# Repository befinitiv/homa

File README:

The goal of this project is to create small, cheap and power efficient devices for home automation (HA).

First, a remote controllable wall socket will be built. This will give the basis for deriving other devices for sensing and actuating.

All devices will be communicating via a power efficient 2.4GHz wireless link. For saving cost and power, a proprietary protocol will be used (http://www.nordicsemi.com/eng/Products/2.4GHz-RF/nRF24L01 ).

Power efficiency is a key goal of the project. By using modern approaches for the power supply, the power consumption of these devices will be two orders of magnitude lower than the usual standby power of consumer devices. The user does not have to think about whether or not to add another HA device. In almost every case adding more HA devices will save power.

----
All prices include VAT.
Edit
Battery powered devel board (rev A)

Components: 5.09€
PCB: 55mmx18mm = 0.1dm^2 = 7€ plus 1€ mill cost
Sum: 13.09€
---
Reduced price for 50x pieces:
Components 1.46€ (future electronics)
PCB: 1.60€ (Fischer PCB, reduced width)
Sum: 3.06€
Edit
STM ucboard (rev A)

Components: 8€
PCB: 34mmx14mm = 0.047dm^2 = 3.29€ plus 1€ mill cost
Sum: 12.29€
---
Reduced price for 50x pieces without LEDs, RTC and 64kB uC:
Components: 1.40€ (future electronics)
PCB: 1.19€ (Fischer PCB)
Sum: 2.59€
Edit
Relais board (rev A)

Components: 8.43€
PCB: 34mmx23mm = 0.078dm^2 = 5.46€ plus 1€ mill cost
Sum: 14.89€

Price for 1dm^2 PCB: 70€ (pcb-pool)
Edit
Log

15-03-19 Cedric paid everything to Bennet

----

SettingUpBuildEnv

    Download compiler:
    sudo add-apt-repository ppa:terry.guo/gcc-arm-embedded
    sudo apt-get update
    sudo apt-get install gcc-arm-none-eabi

    Download and install segger software:
    http://www.segger.com/jlink-software.html?step=2&file=JLinkLinuxDEB64_4.82

    Install Eclipse
        Inside of eclipse: Install GDB Hardware Debugging extension http://stm32discovery.nano-age.co.uk/open-source-development-with-the-stm32-discovery/getting-hardware-debuging-working-with-eclipse-and-code-sourcey
        Create a “GDB hardware debugging” configuration and enter the following lines to “Startup→Initialization Commands”:
        monitor flash device STM32F051C8
        monitor speed 1000

-----

h1. Tea1721

See http://www.nxp.com/documents/user_manual/UM10522.pdf

L1: "Reichelt":http://www.reichelt.de/Power-Induktivitaeten-SMD/L-PISG-1-0M/3/index.html?&ACTION=3&LA=2&ARTICLE=86537&GROUPID=3709&artnr=L-PISG+1%2C0M
L2: "Reichelt":http://www.reichelt.de/Power-Induktivitaeten-SMD/L-PISR-1-0M/3/index.html?&ACTION=3&LA=2&ARTICLE=73077&GROUPID=3709&artnr=L-PISR+1%2C0M

D7: "Digikey":http://www.digikey.de/product-detail/de/BZX384-B12,115/568-3810-1-ND/1163091
D4, D6: "Reichelt":http://www.reichelt.de/BY-BYX-EM-ER-Dioden/ES-1JL-SMD/3/index.html?&ACTION=3&LA=446&ARTICLE=95404&GROUPID=2989&artnr=ES+1JL+SMD
D5: "Digikey":http://www.digikey.de/product-detail/de/BYG20J-E3%2FTR/BYG20J-E3%2FTRGICT-ND/2356593
D1: "Reichelt":http://www.reichelt.de/SB-SKE-4F-Dioden/S-1ML-SMD/3/index.html?&ACTION=3&LA=446&ARTICLE=95358&GROUPID=2991&artnr=S+1ML+SMD

C1,C2: "Digikey":http://www.digikey.de/product-detail/de/400PX4R7MEFCTA8X11.5/1189-1633-1-ND/3134590
C3: "Digikey":http://www.digikey.de/product-detail/de/C0603C100K3GACTU/399-8979-1-ND/3522496
C7: "Digikey":http://www.digikey.de/product-detail/de/CL05B103KB5NNNC/1276-1028-1-ND/3889114
C45, C14: "Digikey":http://www.digikey.de/product-detail/de/CL31A225KB9LNNC/1276-2723-1-ND/3890809
C6: "Digikey":http://www.digikey.de/product-detail/de/UVR1C471MPD/493-1043-ND/588784

IC1: "Digikey":http://www.digikey.de/product-detail/de/TEA1721AT%2FN1,118/568-9556-1-ND/3250102

R1: "Digikey":http://www.digikey.de/product-detail/de/CF14JT47R0/CF14JT47R0CT-ND/1830319
R2: "Digikey":http://www.digikey.de/product-detail/de/RC1005F472CS/1276-3466-1-ND/3903569
R3: "Digikey":http://www.digikey.de/product-detail/de/MCR01MRTF1802/RHM18KCDCT-ND/4083706
R4: "Digikey":http://www.digikey.de/product-detail/de/RC1206JR-071RL/311-1.0ERCT-ND/732132
R5: "Digikey":http://www.digikey.de/product-detail/de/RC0603JR-0768KL/311-68KGRCT-ND/729769

SS-Relais: "Digikey":http://www.digikey.de/product-detail/de/PR3BMF51NSKF/425-2562-5-ND/1302229

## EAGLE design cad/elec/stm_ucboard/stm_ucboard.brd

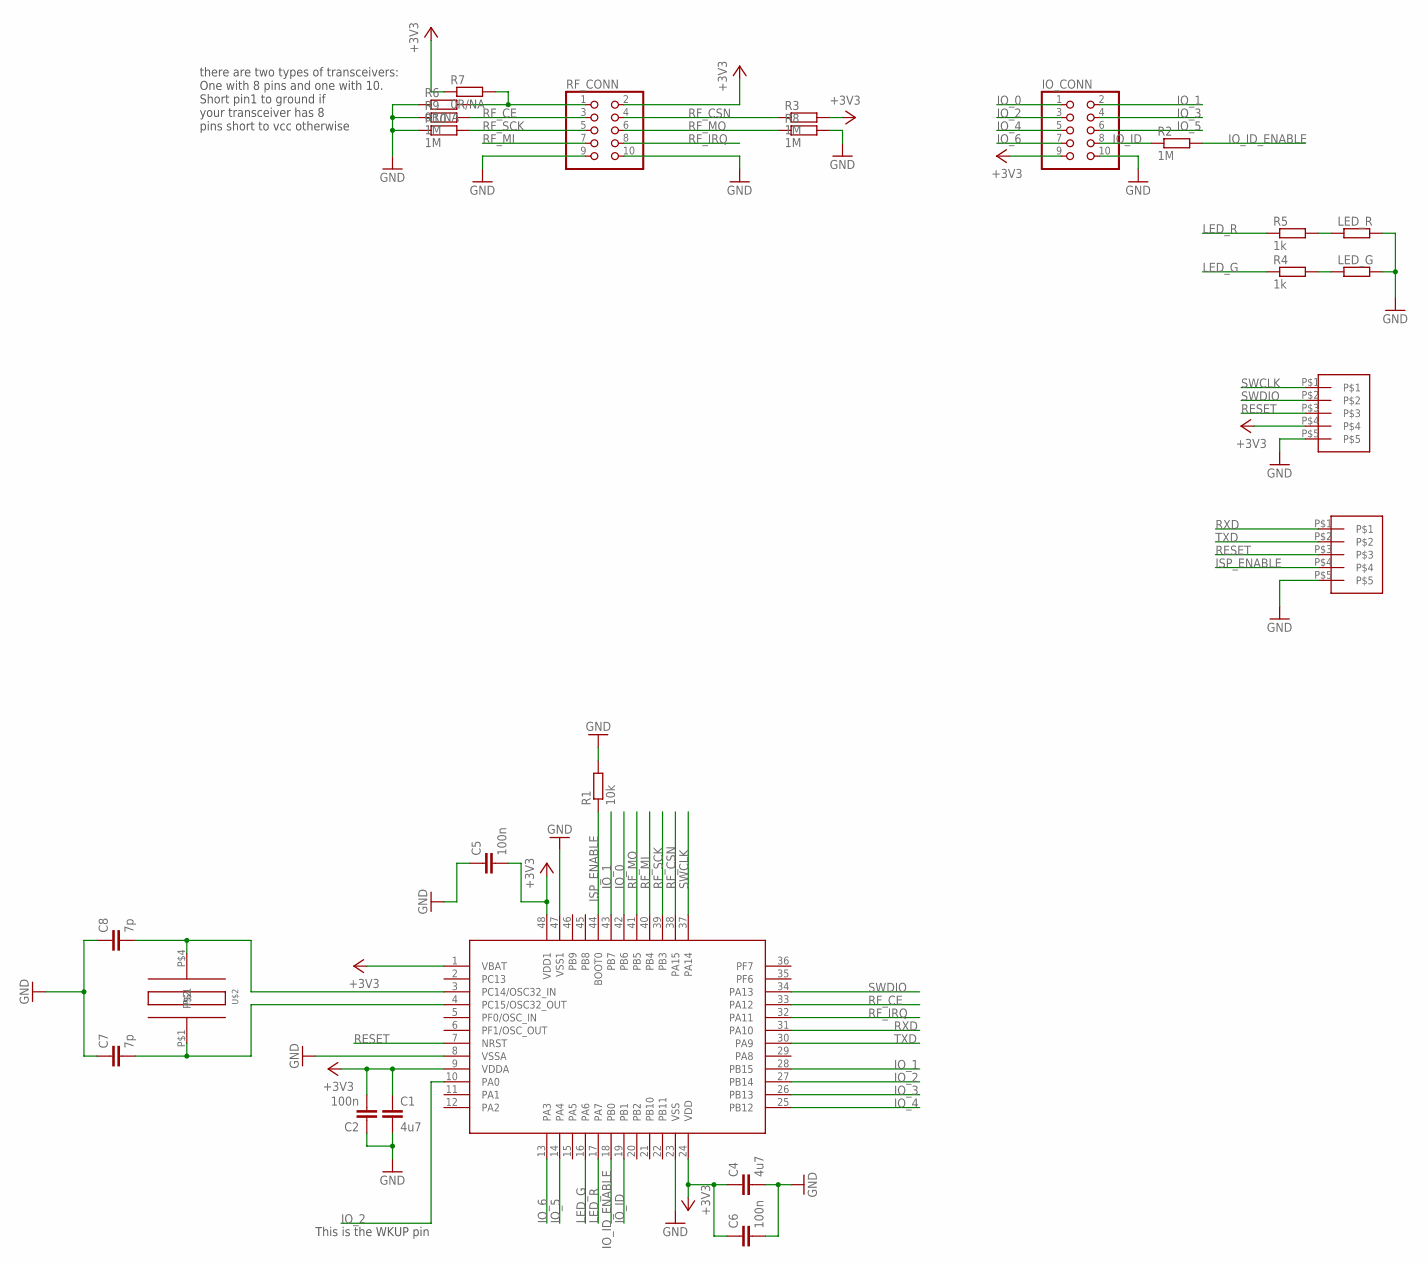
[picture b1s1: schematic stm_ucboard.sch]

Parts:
C1, C4: 4u7; C0603; DIGIKEY 1276-2087-1-ND
C2, C5, C6: 100n; C0603; DIGIKEY 399-1095-1-ND
C7, C8: 7p; C0603; DIGIKEY 1276-2136-1-ND
DBG: 005CONTACTS; 05HEADER; DIGIKEY S9014E-05-ND
IO_CONN: PINHD-2X5; 2X05; DIGIKEY 952-2124-ND
LED_G: R-EU_R0402; R0402; DIGIKEY 754-1101-1-ND
LED_R: R-EU_R0402; R0402; DIGIKEY 754-1104-1-ND
R1: 10k; R0402; DIGIKEY 1276-5086-1-ND
R2, R3, R8, R9, R10: 1M; R0402; DIGIKEY 1276-4448-1-ND
R4, R5: 1k; R0402; DIGIKEY 1276-5062-1-ND
R6, R7: 0R/NA; R0201
RF_CONN: PINHD-2X5; 2X05; DIGIKEY S6105-ND
U$1: STM32F051; LQFP48; DIGIKEY 497-12893-ND
U$2: CRYSTAL_32K; SOJ4; DIGIKEY 370-1056-1-ND
UART: 005CONTACTS; 05HEADER; DIGIKEY S9014E-05-ND

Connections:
+3V3: C1.1, C2.2, C4.1, C5.2, C6.1, DBG.P$4, IO_CONN.9, R3.2, R7.1, RF_CONN.2, U$1.1 (VBAT), U$1.9 (VDDA), U$1.24 (VDD), U$1.48 (VDD1)
GND: C1.2, C2.1, C4.2, C5.1, C6.2, C7.1, C8.1, DBG.P$5, IO_CONN.10, LED_G.2, LED_R.2, R1.2, R6.1, R8.2, R9.1, R10.1, RF_CONN.9, RF_CONN.10, U$1.8 (VSSA), U$1.23 (VSS), U$1.47 (VSS1), UART.P$5
IO_0: IO_CONN.1, U$1.42 (PB6)
IO_1: IO_CONN.2, U$1.28 (PB15), U$1.43 (PB7)
IO_2: IO_CONN.3, U$1.10 (PA0), U$1.27 (PB14)
IO_3: IO_CONN.4, U$1.26 (PB13)
IO_4: IO_CONN.5, U$1.25 (PB12)
IO_5: IO_CONN.6, U$1.14 (PA4)
IO_6: IO_CONN.7, U$1.13 (PA3)
IO_ID: IO_CONN.8, R2.1, U$1.19 (PB1)
IO_ID_ENABLE: R2.2, U$1.18 (PB0)
ISP_ENABLE: R1.1, U$1.44 (BOOT0), UART.P$4
LED_G: R4.1, U$1.16 (PA6)
LED_R: R5.1, U$1.17 (PA7)
unnamed: LED_R.1, R5.2
unnamed: LED_G.1, R4.2
unnamed: C8.2, U$1.3 (PC14/OSC32_IN), U$2.P$4
unnamed: R6.2, R7.2, RF_CONN.1
unnamed: C7.2, U$1.4 (PC15/OSC32_OUT), U$2.P$1
RESET: DBG.P$3, U$1.7 (NRST), UART.P$3
RF_CE: R9.2, RF_CONN.3, U$1.33 (PA12)
RF_CSN: R3.1, RF_CONN.4, U$1.38 (PA15)
RF_IRQ: RF_CONN.8, U$1.32 (PA11)
RF_MI: RF_CONN.7, U$1.40 (PB4)
RF_MO: R8.1, RF_CONN.6, U$1.41 (PB5)
RF_SCK: R10.2, RF_CONN.5, U$1.39 (PB3)
RXD: U$1.31 (PA10), UART.P$1
SWCLK: DBG.P$1, U$1.37 (PA14)
SWDIO: DBG.P$2, U$1.34 (PA13)
TXD: U$1.30 (PA9), UART.P$2

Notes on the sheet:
there are two types of transceivers: One with 8 pins and one with 10. Short pin1 to ground if your transceiver has 8 pins short to vcc otherwise
This is the WKUP pin

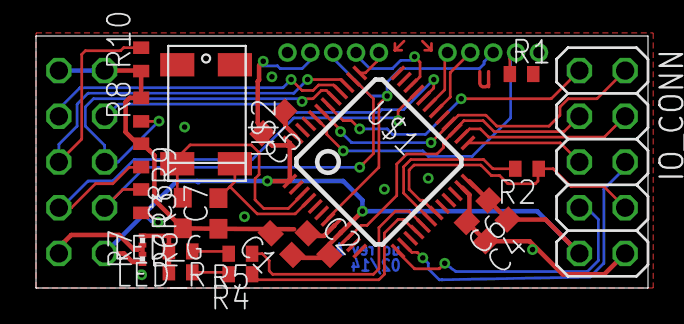
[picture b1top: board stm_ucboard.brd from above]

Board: 2 copper layers, 34.0 x 14.0 mm, 25 parts (1 on the bottom side), 30 nets.

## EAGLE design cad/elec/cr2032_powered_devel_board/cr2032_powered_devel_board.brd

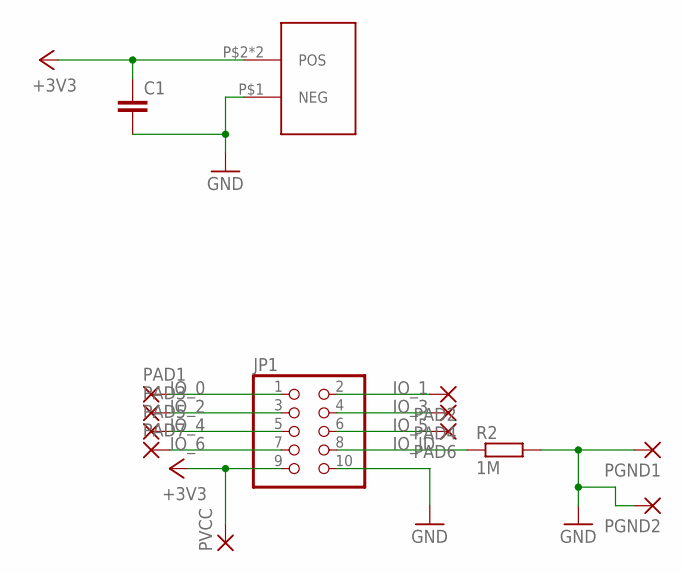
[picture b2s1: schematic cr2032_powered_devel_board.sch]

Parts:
C1: C-EU025-030X050; C025-030X050; DIGIKEY BK-913-ND
JP1: PINHD-2X5; 2X05; DIGIKEY S6105-ND
PAD1, PAD2, PAD3, PAD4, PAD5, PAD6, PAD7: 1,6/0,8
PGND1, PGND2: 1,6/0,8
PVCC: 1,6/0,8
R2: 1M; R0402; DIGIKEY 311-1.00MLRCT-ND
U$1: CR2032_CLIP; DIGIKEY BK-913-ND

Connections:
+3V3: C1.1, JP1.9, PVCC.1, U$1.P$2 (POS), U$1.P$3 (POS)
GND: C1.2, JP1.10, PGND1.1, PGND2.1, R2.2, U$1.P$1 (NEG)
IO_0: JP1.1, PAD1.1
IO_1: JP1.2, PAD2.1
IO_2: JP1.3, PAD3.1
IO_3: JP1.4, PAD4.1
IO_4: JP1.5, PAD5.1
IO_5: JP1.6, PAD6.1
IO_6: JP1.7, PAD7.1
IO_ID: JP1.8, R2.1

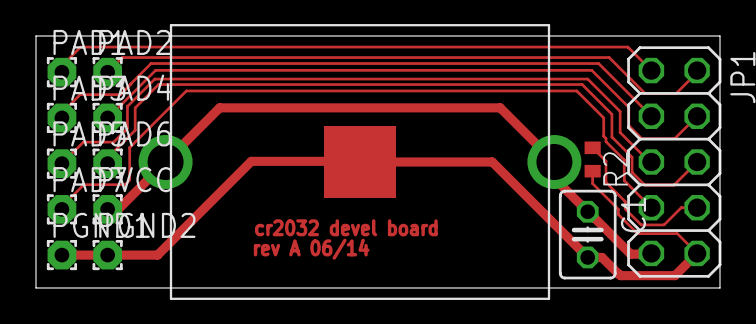
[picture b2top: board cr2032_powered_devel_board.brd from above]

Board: 2 copper layers, 38.0 x 14.0 mm, 14 parts (0 on the bottom side), 10 nets.

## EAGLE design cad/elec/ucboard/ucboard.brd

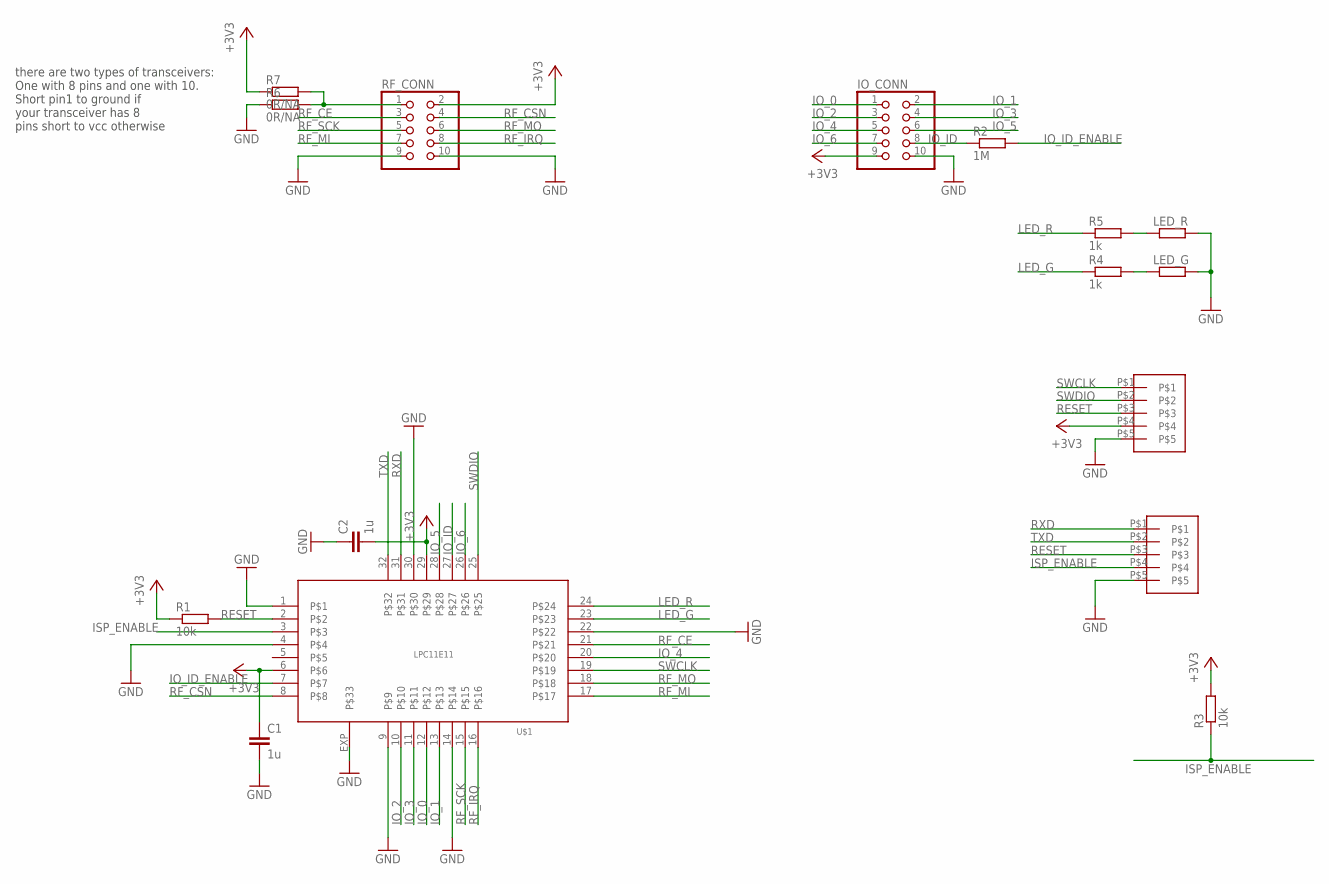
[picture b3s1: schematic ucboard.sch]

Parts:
C1, C2: 1u; C0603; DIGIKEY 1276-1024-1-ND
DBG: 005CONTACTS; 05HEADER
IO_CONN: PINHD-2X5; 2X05
LED_G: R-EU_R0402; R0402; DIGIKEY 754-1101-1-ND
LED_R: R-EU_R0402; R0402; DIGIKEY 754-1104-1-ND
R1, R3: 10k; R0402
R2: 1M; R0402
R4, R5: 1k; R0402
R6, R7: 0R/NA; R0201
RF_CONN: PINHD-2X5; 2X05
U$1: LPC11E14; VQFN32
UART: 005CONTACTS; 05HEADER

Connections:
+3V3: C1.1, C2.2, DBG.P$4, IO_CONN.9, R1.1, R3.2, R7.1, RF_CONN.2, U$1.6, U$1.29
GND: C1.2, C2.1, DBG.P$5, IO_CONN.10, LED_G.2, LED_R.2, R6.1, RF_CONN.9, RF_CONN.10, U$1.1, U$1.4, U$1.9, U$1.14, U$1.22, U$1.30, U$1.EXP, UART.P$5
IO_0: IO_CONN.1, U$1.12
IO_1: IO_CONN.2, U$1.13
IO_2: IO_CONN.3, U$1.10
IO_3: IO_CONN.4, U$1.11
IO_4: IO_CONN.5, U$1.20
IO_5: IO_CONN.6, U$1.28
IO_6: IO_CONN.7, U$1.26
IO_ID: IO_CONN.8, R2.1, U$1.27
IO_ID_ENABLE: R2.2, U$1.7
ISP_ENABLE: R3.1, U$1.3, UART.P$4
LED_G: R4.1, U$1.23
LED_R: R5.1, U$1.24
unnamed: LED_R.1, R5.2
unnamed: LED_G.1, R4.2
unnamed: R6.2, R7.2, RF_CONN.1
RESET: DBG.P$3, R1.2, U$1.2, UART.P$3
RF_CE: RF_CONN.3, U$1.21
RF_CSN: RF_CONN.4, U$1.8
RF_IRQ: RF_CONN.8, U$1.16
RF_MI: RF_CONN.7, U$1.17
RF_MO: RF_CONN.6, U$1.18
RF_SCK: RF_CONN.5, U$1.15
RXD: U$1.31, UART.P$1
SWCLK: DBG.P$1, U$1.19
SWDIO: DBG.P$2, U$1.25
TXD: U$1.32, UART.P$2

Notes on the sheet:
there are two types of transceivers: One with 8 pins and one with 10. Short pin1 to ground if your transceiver has 8 pins short to vcc otherwise

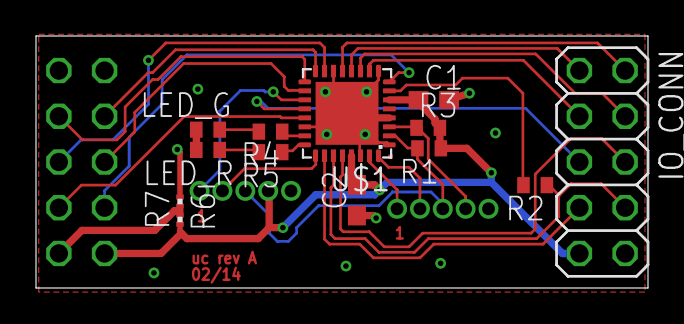
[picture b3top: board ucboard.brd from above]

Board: 2 copper layers, 34.0 x 14.0 mm, 16 parts (1 on the bottom side), 28 nets.

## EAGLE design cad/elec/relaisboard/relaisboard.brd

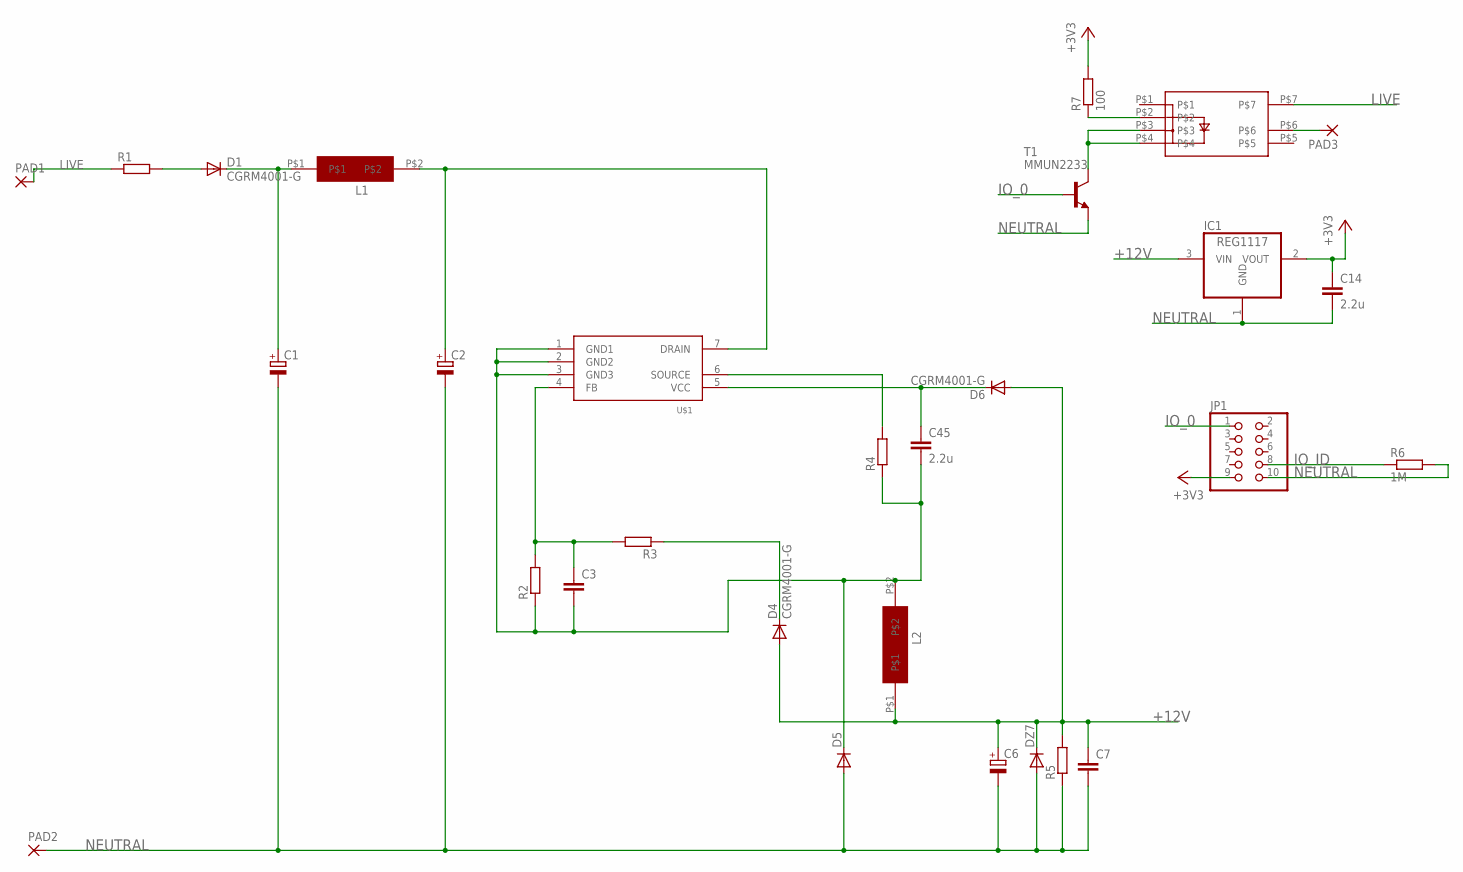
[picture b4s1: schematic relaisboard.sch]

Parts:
C1, C2: CPOL-EUE5-8.5; E5-8,5; DIGIKEY 1189-1633-1-ND
C3: C-EUC0603; C0603; DIGIKEY 399-8979-1-ND
C6: CPOL-EUE3.5-8; E3,5-8; DIGIKEY 493-1043-ND
C7: C-EUC0402; C0402; DIGIKEY 1276-1028-1-ND
C14, C45: 2.2u; C1206; DIGIKEY 1276-2723-1-ND
D1, D4, D6: CGRM4001-G; SOD-123_MINI-SMA
D5: DIODE-DO-214AC; DO-214AC; DIGIKEY BYG20J-E3/TRGICT-ND
DZ7: DIODE-SOD323-R; SOD323-R; DIGIKEY 568-3810-1-ND
IC1: REG1117; SOT223; DIGIKEY AP1117IE33G-13DICT-ND
JP1: PINHD-2X5; 2X05
L1, L2: INDUCTOR
PAD1, PAD2, PAD3: 2,15/1,0
R1: R-EU_0207/2V; 0207/2V; DIGIKEY CF14JT47R0CT-ND
R2: R-EU_R0402; R0402; DIGIKEY 1276-3466-1-ND
R3: R-EU_R0402; R0402; DIGIKEY RHM18KCDCT-ND
R4: R-EU_R1206; R1206; DIGIKEY 311-1.0ERCT-ND
R5: R-EU_R0603; R0603; DIGIKEY 311-68KGRCT-ND
R6: 1M; R0402; DIGIKEY 311-1.00MLRCT-ND
R7: 100; R0402; DIGIKEY 311-100JRCT-ND
T1: MMUN2233; SOT23-BEC; DIGIKEY MMUN2233LT1GOSCT-ND
U$1: TEA1721; SO7; DIGIKEY 568-9556-1-ND
U$2: PR3BMF51; DIP7; DIGIKEY 425-2562-5-ND

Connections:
+3V3: C14.1, IC1.2 (VOUT), JP1.9, R7.2
+12V: C6.+, C7.1, D4.A, D6.A, DZ7.C, IC1.3 (VIN), L2.P$1, R5.2
IO_0: JP1.1, T1.B
IO_ID: JP1.8, R6.1
LIVE: PAD1.1, R1.1, U$2.P$7
unnamed: D1.A, R1.2
unnamed: C1.+, D1.C, L1.P$1
unnamed: C2.+, L1.P$2, U$1.7 (DRAIN)
unnamed: PAD3.1, U$2.P$6
unnamed: R7.1, U$2.P$2
unnamed: T1.C, U$2.P$3, U$2.P$4
unnamed: C45.1, D6.C, U$1.5 (VCC)
unnamed: R4.2, U$1.6 (SOURCE)
unnamed: C3.2, C45.2, D5.C, L2.P$2, R2.1, R4.1, U$1.1 (GND1), U$1.2 (GND2), U$1.3 (GND3)
unnamed: D4.C, R3.1
unnamed: C3.1, R2.2, R3.2, U$1.4 (FB)
NEUTRAL: C1.-, C2.-, C6.-, C7.2, C14.2, D5.A, DZ7.A, IC1.1 (GND), JP1.10, PAD2.1, R5.1, R6.2, T1.E

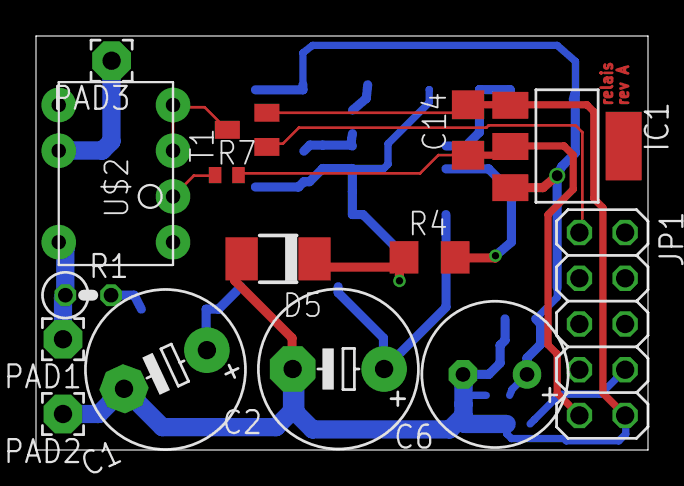
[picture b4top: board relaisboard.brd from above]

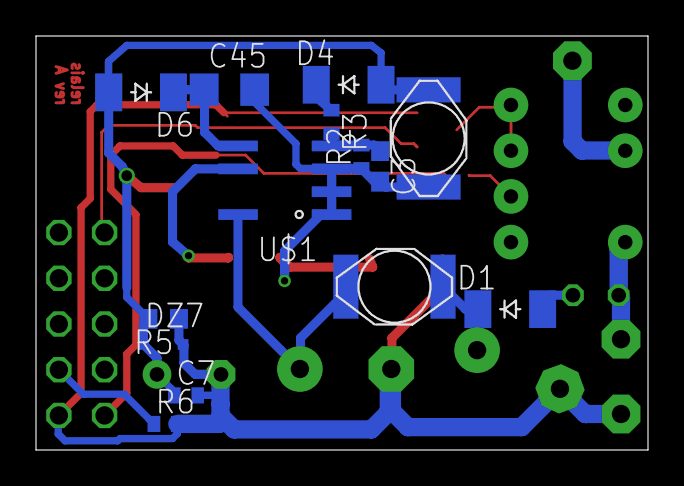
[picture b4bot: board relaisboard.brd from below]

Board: 2 copper layers, 34.0 x 23.0 mm, 29 parts (14 on the bottom side), 17 nets.

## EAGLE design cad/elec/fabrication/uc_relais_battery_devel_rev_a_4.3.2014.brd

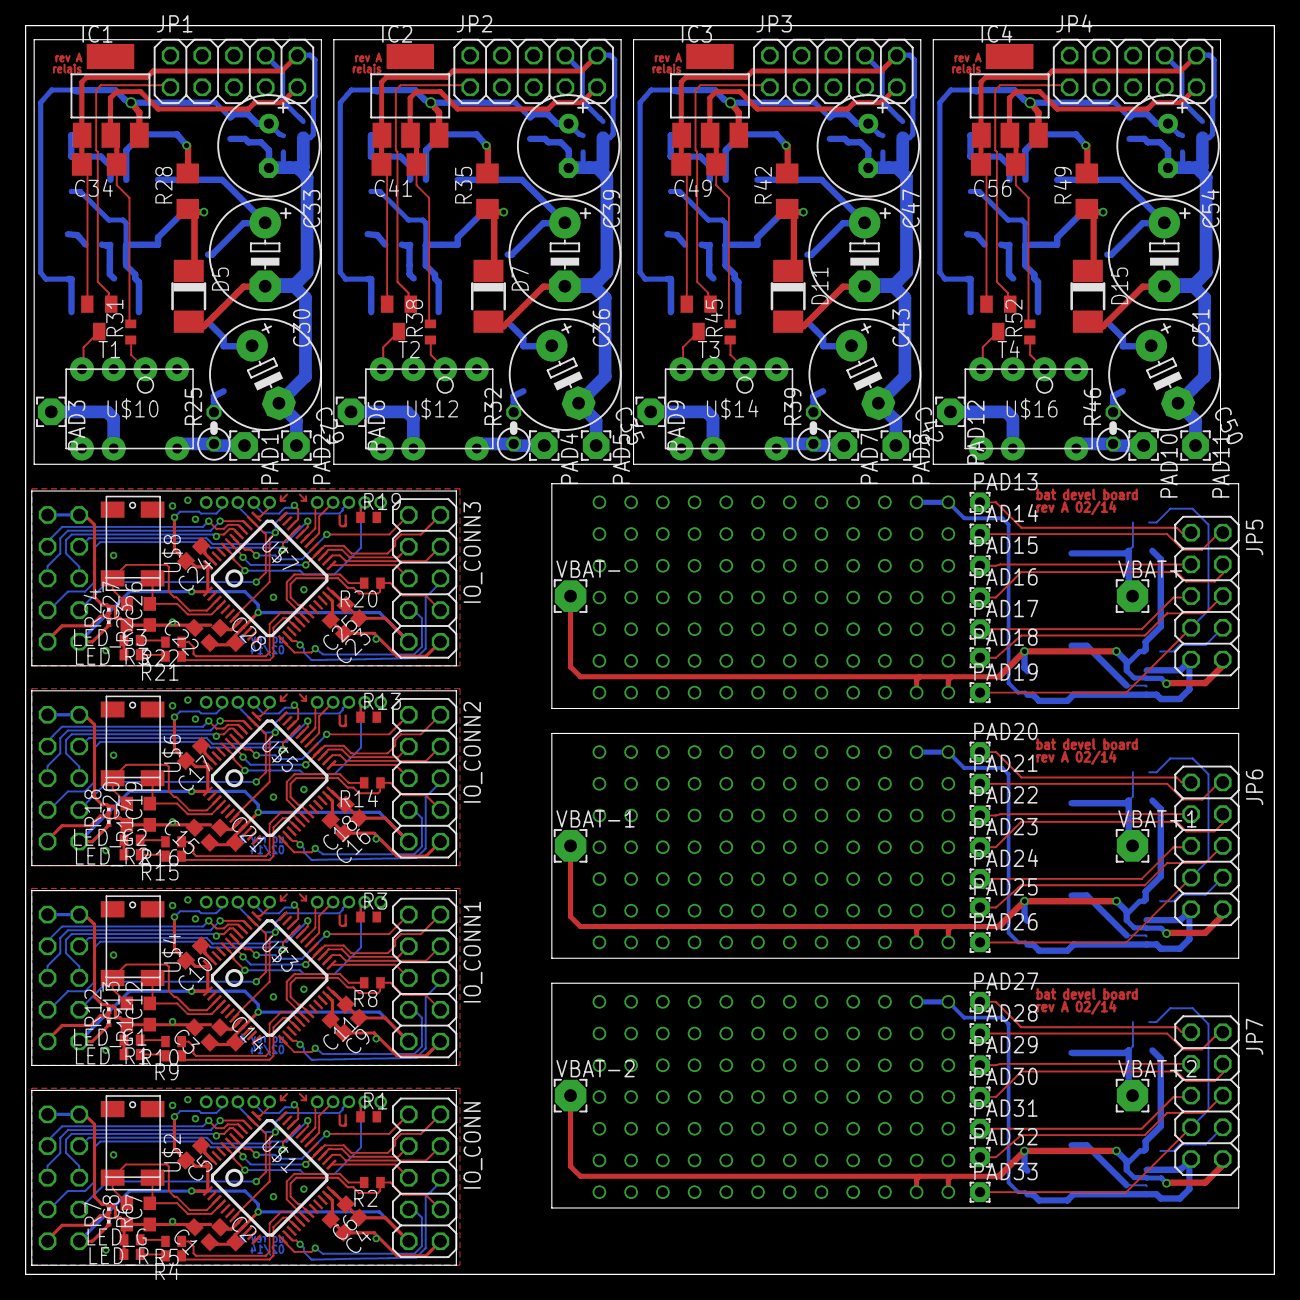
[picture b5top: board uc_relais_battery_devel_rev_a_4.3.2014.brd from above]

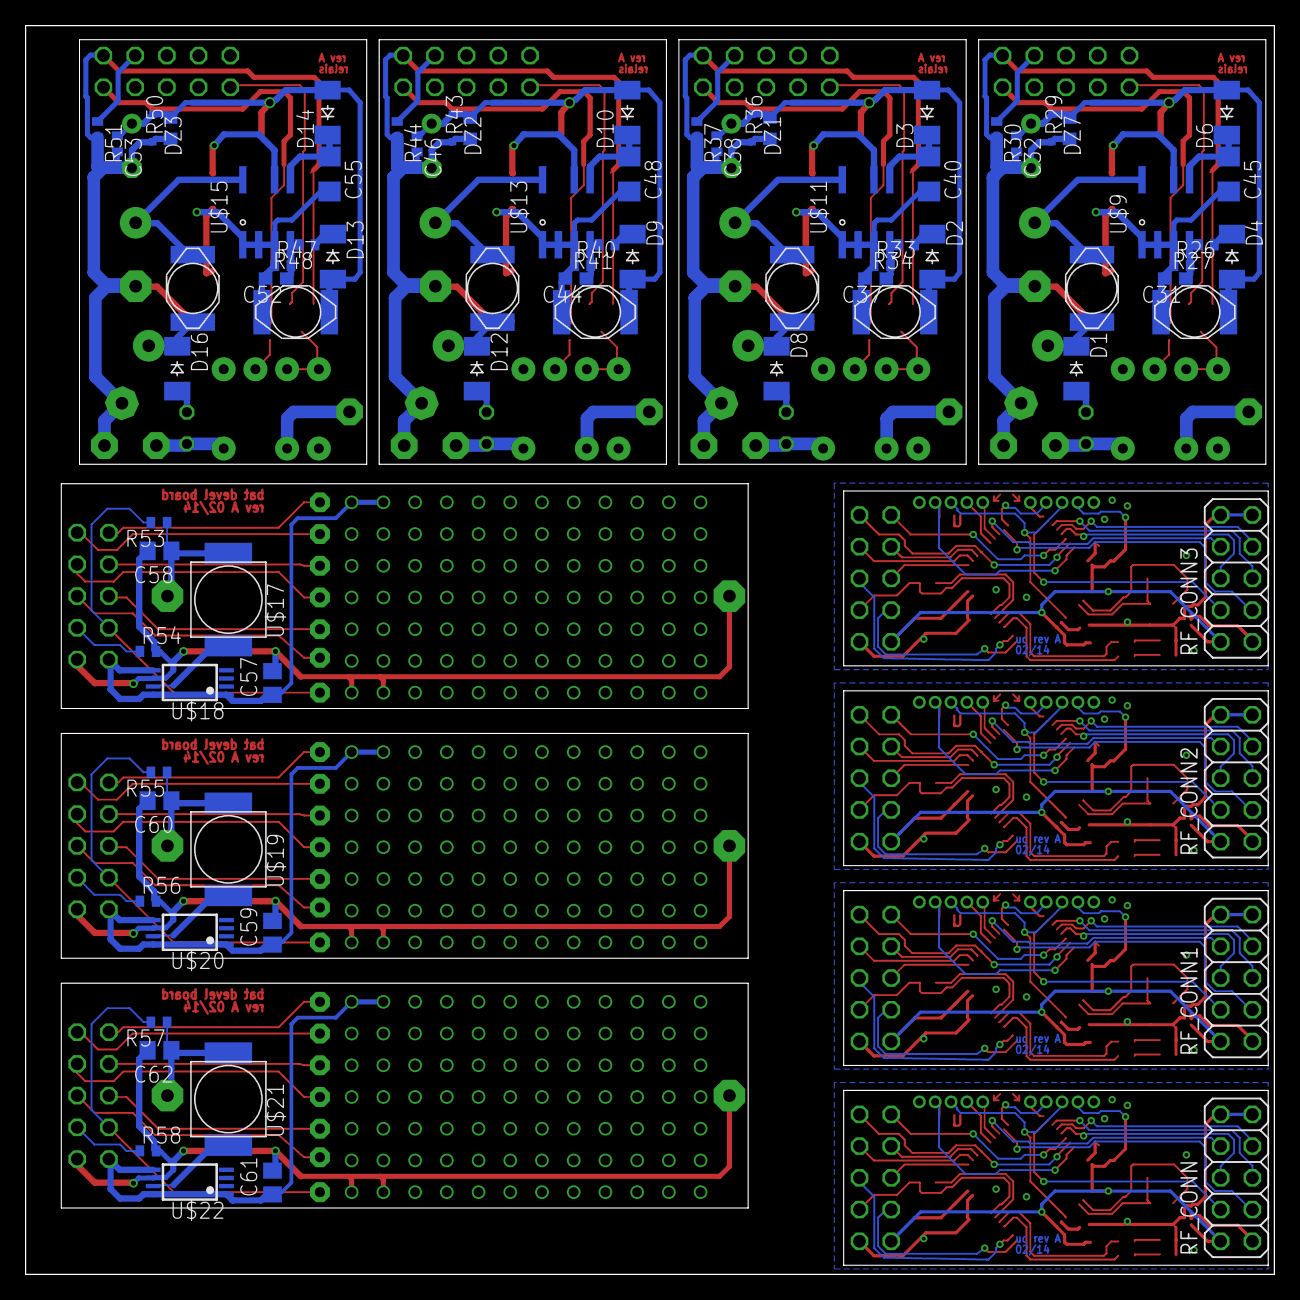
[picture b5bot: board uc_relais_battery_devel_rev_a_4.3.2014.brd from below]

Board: 2 copper layers, 100.0 x 100.0 mm, 248 parts (78 on the bottom side), 224 nets.

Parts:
C1, C3, C4, C9, C15, C16, C22, C23: 4u7; C0603
C2, C5, C6, C10, C11, C14, C17, C18, C21, C24, C25, C28: 100n; C0603
C7, C8, C12, C13, C19, C20, C26, C27: 7p; C0603
C29, C30, C35, C36, C42, C43, C50, C51: E5-8,5
C31, C37, C44, C52: C0603
C32, C38, C46, C53: C0402
C33, C39, C47, C54: E3,5-8
C34, C40, C41, C45, C48, C49, C55, C56: 2.2u; C1206
C57, C58, C59, C60, C61, C62: 22u; C0805
D1, D2, D3, D4, D6, D8, D9, D10, D12, D13, D14, D16: CGRM4001-G; SOD-123_MINI-SMA
D5, D7, D11, D15: DO-214AC
DBG, DBG1, DBG2, DBG3: 05HEADER
DZ1, DZ2, DZ3, DZ7: SOD323-R
IC1, IC2, IC3, IC4: REG1117; SOT223
IO_CONN, IO_CONN1, IO_CONN2, IO_CONN3: 2X05
JP1, JP2, JP3, JP4, JP5, JP6, JP7: 2X05
L1, L2, L3, L4, L5, L6, L7, L8: INDUCTOR
LED_G, LED_G1, LED_G2, LED_G3: R0402
LED_R, LED_R1, LED_R2, LED_R3: R0402
PAD1, PAD2, PAD3, PAD4, PAD5, PAD6, PAD7, PAD8, PAD9, PAD10, PAD11, PAD12: 2,15/1,0
PAD13, PAD14, PAD15, PAD16, PAD17, PAD18, PAD19, PAD20, PAD21, PAD22, PAD23, PAD24, PAD25, PAD26, PAD27, PAD28, PAD29, PAD30, PAD31, PAD32, PAD33: 1,6/0,8
R1, R3, R13, R19: 10k; R0402
R2, R8, R14, R20, R30, R37, R44, R51, R54, R56, R58: 1M; R0402
R4, R5, R9, R10, R15, R16, R21, R22: 1k; R0402
R6, R7, R11, R12, R17, R18, R23, R24: 0R/NA; R0201
R25, R32, R39, R46: 0207/2V
R26, R27, R33, R34, R40, R41, R47, R48: R0402
R28, R35, R42, R49: R1206
R29, R36, R43, R50: R0603
R31, R38, R45, R52: 100; R0402
R53, R55, R57: 0; R0402
RF_CONN, RF_CONN1, RF_CONN2, RF_CONN3: 2X05
T1, T2, T3, T4: MMUN2233; SOT23-BEC
U$1, U$3, U$5, U$7: STM32F051; LQFP48
U$2, U$4, U$6, U$8: CRYSTAL_32K; SOJ4
U$9, U$11, U$13, U$15: TEA1721; SO7
U$10, U$12, U$14, U$16: PR3BMF51; DIP7
U$17, U$19, U$21: ELL_INDUCTOR; ELL6_INDUCTOR
U$18, U$20, U$22: L6920; TSSOP8
UART, UART1, UART2, UART3: 05HEADER
VBAT+, VBAT+1, VBAT+2: 2,54/1,0
VBAT-, VBAT-1, VBAT-2: 2,54/1,0

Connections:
+3V1: C3.1, C9.1, C10.2, C11.1, C14.2, DBG1.P$4, IO_CONN1.9, R12.1, RF_CONN1.2, U$3.1, U$3.9, U$3.24, U$3.48
+3V2: C15.1, C16.1, C17.2, C18.1, C21.2, DBG2.P$4, IO_CONN2.9, R18.1, RF_CONN2.2, U$5.1, U$5.9, U$5.24, U$5.48
+3V3: C1.1, C2.2, C4.1, C5.2, C6.1, DBG.P$4, IO_CONN.9, R7.1, RF_CONN.2, U$1.1, U$1.9, U$1.24, U$1.48
+3V4: C22.1, C23.1, C24.2, C25.1, C28.2, DBG3.P$4, IO_CONN3.9, R24.1, RF_CONN3.2, U$7.1, U$7.9, U$7.24, U$7.48
+3V5: C34.1, IC1.2, JP1.9, R31.2
+3V6: C41.1, IC2.2, JP2.9, R38.2
+3V7: C49.1, IC3.2, JP3.9, R45.2
+3V8: C56.1, IC4.2, JP4.9, R52.2
+3V9: C57.1, JP5.9, U$18.1, U$18.5, U$18.8
+3V10: C59.1, JP6.9, U$20.1, U$20.5, U$20.8
+3V11: C61.1, JP7.9, U$22.1, U$22.5, U$22.8
+12V: C32.1, C33.+, D4.A, D6.A, DZ7.C, IC1.3, L2.P$1, R29.2
+12V1: C38.1, C39.+, D2.A, D3.A, DZ1.C, IC2.3, L4.P$1, R36.2
+12V2: C46.1, C47.+, D9.A, D10.A, DZ2.C, IC3.3, L6.P$1, R43.2
+12V3: C53.1, C54.+, D13.A, D14.A, DZ3.C, IC4.3, L8.P$1, R50.2
GND: C1.2, C2.1, C4.2, C5.1, C6.2, C7.1, C8.1, DBG.P$5, IO_CONN.10, LED_G.2, LED_R.2, R1.2, R6.1, RF_CONN.9, RF_CONN.10, U$1.8, U$1.23, U$1.47, UART.P$5
GND1: C3.2, C9.2, C10.1, C11.2, C12.1, C13.1, C14.1, DBG1.P$5, IO_CONN1.10, LED_G1.2, LED_R1.2, R3.2, R11.1, RF_CONN1.9, RF_CONN1.10, U$3.8, U$3.23, U$3.47, UART1.P$5
GND2: C15.2, C16.2, C17.1, C18.2, C19.1, C20.1, C21.1, DBG2.P$5, IO_CONN2.10, LED_G2.2, LED_R2.2, R13.2, R17.1, RF_CONN2.9, RF_CONN2.10, U$5.8, U$5.23, U$5.47, UART2.P$5
GND3: C22.2, C23.2, C24.1, C25.2, C26.1, C27.1, C28.1, DBG3.P$5, IO_CONN3.10, LED_G3.2, LED_R3.2, R19.2, R23.1, RF_CONN3.9, RF_CONN3.10, U$7.8, U$7.23, U$7.47, UART3.P$5
GND4: C57.2, C58.2, JP5.10, R54.2, U$18.6, VBAT-.1
GND5: C59.2, C60.2, JP6.10, R56.2, U$20.6, VBAT-1.1
GND6: C61.2, C62.2, JP7.10, R58.2, U$22.6, VBAT-2.1
IO_0: IO_CONN.1, U$1.42
IO_1: IO_CONN.2, U$1.28, U$1.43
IO_2: IO_CONN.3, U$1.27
IO_3: IO_CONN.4, U$1.26
IO_4: IO_CONN.5, U$1.25
IO_5: IO_CONN.6, U$1.14
IO_6: IO_CONN.7, U$1.13
IO_7: IO_CONN1.7, U$3.13
IO_8: IO_CONN1.6, U$3.14
IO_9: IO_CONN1.1, U$3.42
IO_10: IO_CONN1.5, U$3.25
IO_11: IO_CONN1.4, U$3.26
IO_12: IO_CONN1.3, U$3.27
IO_13: IO_CONN1.2, U$3.28, U$3.43
IO_14: IO_CONN2.7, U$5.13
IO_15: IO_CONN2.6, U$5.14
IO_16: IO_CONN2.1, U$5.42
IO_17: IO_CONN2.5, U$5.25
IO_18: IO_CONN2.4, U$5.26
IO_19: IO_CONN2.3, U$5.27
IO_20: IO_CONN2.2, U$5.28, U$5.43
IO_21: IO_CONN3.7, U$7.13
IO_22: IO_CONN3.6, U$7.14
IO_23: IO_CONN3.1, U$7.42
IO_24: IO_CONN3.5, U$7.25
IO_25: IO_CONN3.4, U$7.26
IO_26: IO_CONN3.3, U$7.27
IO_27: IO_CONN3.2, U$7.28, U$7.43
IO_28: JP1.1, T1.B
IO_29: JP2.1, T2.B
IO_30: JP3.1, T3.B
IO_31: JP4.1, T4.B
IO_32: JP5.1, PAD13.1
IO_33: JP5.3, PAD15.1
IO_34: JP5.5, PAD17.1
IO_35: JP5.7, PAD19.1, R53.2
IO_36: JP5.2, PAD14.1
IO_37: JP5.4, PAD16.1
IO_38: JP5.6, PAD18.1
IO_39: JP6.1, PAD20.1
IO_40: JP6.3, PAD22.1
IO_41: JP6.5, PAD24.1
IO_42: JP6.7, PAD26.1, R55.2
IO_43: JP6.2, PAD21.1
IO_44: JP6.4, PAD23.1
IO_45: JP6.6, PAD25.1
IO_46: JP7.1, PAD27.1
IO_47: JP7.3, PAD29.1
IO_48: JP7.5, PAD31.1
IO_49: JP7.7, PAD33.1, R57.2
IO_50: JP7.2, PAD28.1
IO_51: JP7.4, PAD30.1
IO_52: JP7.6, PAD32.1
IO_ID: IO_CONN.8, R2.1, U$1.19
IO_ID1: IO_CONN1.8, R8.1, U$3.19
IO_ID2: IO_CONN2.8, R14.1, U$5.19
IO_ID3: IO_CONN3.8, R20.1, U$7.19
IO_ID4: JP1.8, R30.1
IO_ID5: JP2.8, R37.1
IO_ID6: JP3.8, R44.1
IO_ID7: JP4.8, R51.1
IO_ID8: JP5.8, R54.1
IO_ID9: JP6.8, R56.1
IO_ID10: JP7.8, R58.1
IO_ID_ENABLE: R2.2, U$1.18
IO_ID_ENABLE1: R8.2, U$3.18
IO_ID_ENABLE2: R14.2, U$5.18
IO_ID_ENABLE3: R20.2, U$7.18
ISP_ENABLE: R1.1, U$1.44, UART.P$4
ISP_ENABLE1: R3.1, U$3.44, UART1.P$4
ISP_ENABLE2: R13.1, U$5.44, UART2.P$4
ISP_ENABLE3: R19.1, U$7.44, UART3.P$4
LED_G: R4.1, U$1.16
LED_G1: R9.1, U$3.16
LED_G2: R15.1, U$5.16
LED_G3: R21.1, U$7.16
LED_R: R5.1, U$1.17
LED_R1: R10.1, U$3.17
LED_R2: R16.1, U$5.17
LED_R3: R22.1, U$7.17
LIVE: PAD1.1, R25.1, U$10.P$7
LIVE1: PAD4.1, R32.1, U$12.P$7
LIVE2: PAD7.1, R39.1, U$14.P$7
LIVE3: PAD10.1, R46.1, U$16.P$7
unnamed: LED_R.1, R5.2
unnamed: LED_G.1, R4.2
unnamed: C8.2, U$1.3, U$2.P$4
unnamed: R6.2, R7.2, RF_CONN.1
unnamed: C7.2, U$1.4, U$2.P$1
unnamed: LED_R1.1, R10.2
unnamed: LED_G1.1, R9.2
unnamed: R11.2, R12.2, RF_CONN1.1
unnamed: C13.2, U$3.3, U$4.P$4
unnamed: C12.2, U$3.4, U$4.P$1
unnamed: LED_R2.1, R16.2
unnamed: LED_G2.1, R15.2
unnamed: R17.2, R18.2, RF_CONN2.1
unnamed: C20.2, U$5.3, U$6.P$4
unnamed: C19.2, U$5.4, U$6.P$1
unnamed: LED_R3.1, R22.2
unnamed: LED_G3.1, R21.2
unnamed: R23.2, R24.2, RF_CONN3.1
unnamed: C27.2, U$7.3, U$8.P$4
unnamed: C26.2, U$7.4, U$8.P$1
unnamed: D1.A, R25.2
unnamed: C29.+, D1.C, L1.P$1
unnamed: C30.+, L1.P$2, U$9.7
unnamed: C45.1, D6.C, U$9.5
unnamed: R28.2, U$9.6
unnamed: C31.2, C45.2, D5.C, L2.P$2, R26.1, R28.1, U$9.1, U$9.2, U$9.3
unnamed: D4.C, R27.1
unnamed: C31.1, R26.2, R27.2, U$9.4
unnamed: PAD3.1, U$10.P$6
unnamed: R31.1, U$10.P$2
unnamed: T1.C, U$10.P$3, U$10.P$4
unnamed: D8.A, R32.2
unnamed: C35.+, D8.C, L3.P$1
unnamed: C36.+, L3.P$2, U$11.7
unnamed: C40.1, D3.C, U$11.5
unnamed: R35.2, U$11.6
unnamed: C37.2, C40.2, D7.C, L4.P$2, R33.1, R35.1, U$11.1, U$11.2, U$11.3
unnamed: D2.C, R34.1
unnamed: C37.1, R33.2, R34.2, U$11.4
unnamed: PAD6.1, U$12.P$6
unnamed: R38.1, U$12.P$2
unnamed: T2.C, U$12.P$3, U$12.P$4
unnamed: D12.A, R39.2
unnamed: C42.+, D12.C, L5.P$1
unnamed: C43.+, L5.P$2, U$13.7
unnamed: C48.1, D10.C, U$13.5
unnamed: R42.2, U$13.6
unnamed: C44.2, C48.2, D11.C, L6.P$2, R40.1, R42.1, U$13.1, U$13.2, U$13.3
unnamed: D9.C, R41.1
unnamed: C44.1, R40.2, R41.2, U$13.4
unnamed: PAD9.1, U$14.P$6
unnamed: R45.1, U$14.P$2
unnamed: T3.C, U$14.P$3, U$14.P$4
unnamed: D16.A, R46.2
unnamed: C50.+, D16.C, L7.P$1
unnamed: C51.+, L7.P$2, U$15.7
unnamed: C55.1, D14.C, U$15.5
unnamed: R49.2, U$15.6
unnamed: C52.2, C55.2, D15.C, L8.P$2, R47.1, R49.1, U$15.1, U$15.2, U$15.3
unnamed: D13.C, R48.1
unnamed: C52.1, R47.2, R48.2, U$15.4
unnamed: PAD12.1, U$16.P$6
unnamed: R52.1, U$16.P$2
unnamed: T4.C, U$16.P$3, U$16.P$4
unnamed: U$17.P$1, U$18.7
unnamed: U$19.P$1, U$20.7
unnamed: U$21.P$1, U$22.7
NEUTRAL: C29.-, C30.-, C32.2, C33.-, C34.2, D5.A, DZ7.A, IC1.1, JP1.10, PAD2.1, R29.1, R30.2, T1.E
NEUTRAL1: C35.-, C36.-, C38.2, C39.-, C41.2, D7.A, DZ1.A, IC2.1, JP2.10, PAD5.1, R36.1, R37.2, T2.E
NEUTRAL2: C42.-, C43.-, C46.2, C47.-, C49.2, D11.A, DZ2.A, IC3.1, JP3.10, PAD8.1, R43.1, R44.2, T3.E
NEUTRAL3: C50.-, C51.-, C53.2, C54.-, C56.2, D15.A, DZ3.A, IC4.1, JP4.10, PAD11.1, R50.1, R51.2, T4.E
RESET: DBG.P$3, U$1.7, UART.P$3
RESET1: DBG1.P$3, U$3.7, UART1.P$3
RESET2: DBG2.P$3, U$5.7, UART2.P$3
RESET3: DBG3.P$3, U$7.7, UART3.P$3
RF_CE: RF_CONN.3, U$1.33
RF_CE1: RF_CONN1.3, U$3.33
RF_CE2: RF_CONN2.3, U$5.33
RF_CE3: RF_CONN3.3, U$7.33
RF_CSN: RF_CONN.4, U$1.38
RF_CSN1: RF_CONN1.4, U$3.38
RF_CSN2: RF_CONN2.4, U$5.38
RF_CSN3: RF_CONN3.4, U$7.38
RF_IRQ: RF_CONN.8, U$1.32
RF_IRQ1: RF_CONN1.8, U$3.32
RF_IRQ2: RF_CONN2.8, U$5.32
RF_IRQ3: RF_CONN3.8, U$7.32
RF_MI: RF_CONN.7, U$1.40
RF_MI1: RF_CONN1.7, U$3.40
RF_MI2: RF_CONN2.7, U$5.40
RF_MI3: RF_CONN3.7, U$7.40
RF_MO: RF_CONN.6, U$1.41
RF_MO1: RF_CONN1.6, U$3.41
RF_MO2: RF_CONN2.6, U$5.41
RF_MO3: RF_CONN3.6, U$7.41
RF_SCK: RF_CONN.5, U$1.39
RF_SCK1: RF_CONN1.5, U$3.39
RF_SCK2: RF_CONN2.5, U$5.39
RF_SCK3: RF_CONN3.5, U$7.39
RXD: U$1.31, UART.P$1
RXD1: U$3.31, UART1.P$1
RXD2: U$5.31, UART2.P$1
RXD3: U$7.31, UART3.P$1
SWCLK: DBG.P$1, U$1.37
SWCLK1: DBG1.P$1, U$3.37
SWCLK2: DBG2.P$1, U$5.37
SWCLK3: DBG3.P$1, U$7.37
SWDIO: DBG.P$2, U$1.34
SWDIO1: DBG1.P$2, U$3.34
SWDIO2: DBG2.P$2, U$5.34
SWDIO3: DBG3.P$2, U$7.34
TXD: U$1.30, UART.P$2
TXD1: U$3.30, UART1.P$2
TXD2: U$5.30, UART2.P$2
TXD3: U$7.30, UART3.P$2
VBAT: C58.1, R53.1, U$17.P$2, VBAT+.1
VBAT1: C60.1, R55.1, U$19.P$2, VBAT+1.1
VBAT2: C62.1, R57.1, U$21.P$2, VBAT+2.1

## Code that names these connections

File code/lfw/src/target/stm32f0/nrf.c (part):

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static uint8_t g_reg_config = 0;

static void nrf_ce(void) {
	gpio_set(PORT_RF_CE, PIN_RF_CE);
}

static void nrf_nce(void) {
	gpio_clear(PORT_RF_CE, PIN_RF_CE);
}

static uint8_t nrf_write_data(uint8_t command, const uint8_t *data, uint8_t len) {
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static void nrf_init_hardware(void)
{
	RCC_AHBENR |= RCC_AHBENR_GPIOAEN;
	gpio_mode_setup(PORT_RF_CE, GPIO_MODE_OUTPUT, GPIO_PUPD_NONE, PIN_RF_CE);
	nrf_nce();
}

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	if(!PWR_WAS_I_IN_STANDBY) {
		nrf_init_chip_settings();
	}
	gpio_registerFor_interrupt(&on_irqLine, PORT_RF_IRQ, PIN_RF_IRQ, GPIO_TRIGGER_LEVEL_FALLING, NULL);
	gpio_enable_interrupt(PORT_RF_IRQ, PIN_RF_IRQ);
}

nrfPipeHandle_t nrf_setupNewRxDataPipe(uint8_t pipeAddr, uint8_t packetLen, nrfReceiveCallback_t receiveCallback, bool autoAck)
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			nrf_write_data(NRF_W_TX_PAYLOAD, packetBuf, packetBufLen);

			/* trigger sending of packet by pulsing the cs pin */
			gpio_set(PORT_RF_CE, PIN_RF_CE);
			for (unsigned int i = 0; i < (1U << 10); ++i) {
				__asm__ volatile ("nop");
			}
			gpio_clear(PORT_RF_CE, PIN_RF_CE);

			int pinstatus = gpio_get(PORT_RF_IRQ, PIN_RF_IRQ);
			uint8_t statusReg;
			nrf_read_register(NRF_STATUS, &statusReg, sizeof(statusReg));
			__asm__ volatile ("nop");
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
		//bottom
		if(key == 0x1e) {
			gpio_clear(PORT_LED, PIN_LED_R);
			gpio_clear(PORT_IO_0, PIN_IO_0);
		} else if(key == 0xf) { //middle
			gpio_set(PORT_LED, PIN_LED_R);
			gpio_set(PORT_IO_0, PIN_IO_0);
		}

	}
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		UNUSED(blubb1);
		UNUSED(blubb2);
		if(blubb1 == 0x1e) {
				gpio_clear(PORT_LED, PIN_LED_G);
				gpio_clear(PORT_IO_0, PIN_IO_0);
		} else if(blubb1 == 0xf) { //middle
				gpio_set(PORT_LED, PIN_LED_G);
				gpio_set(PORT_IO_0, PIN_IO_0);
		}

	}
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	nrf_setRxBaseAddress(&baseAddr, 2);
	nrf_setupNewRxDataPipe(0xe7, 2, &testPipeRxCallback, false);

	gpio_mode_setup(PORT_LED, GPIO_MODE_OUTPUT, GPIO_PUPD_NONE, PIN_LED_G);
	gpio_clear(PORT_LED, PIN_LED_G);

//	const char packet[] = "Hallo Welt";
//	nrf_sendPacket(&baseAddr, sizeof(baseAddr), packet, sizeof(packet), true, 0);
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
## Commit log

2014-02-18 added IO_ID_ENABLE. fixed IO_1 line
2014-02-23 added two solder bridges to be attach ether the 8 pin transceiver or the 10 pin transceiver (they are almost pin compatible) and exchanged the connectors for dummy 0.05 inch holes. A debug/flash util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
2014-02-23 added gitignore cause of those super stupid extra files eagle generates...
2014-02-23 added power supply schematics and spice simulation files
2014-02-25 added pr3bm51 relais
2014-02-25 first version of relaisboard done
2014-02-25 changed track to be further away from cap
2014-02-26 increased cleareance here and there
2014-02-27 fixed merge issue
2014-02-27 increased cleareance... again
2014-02-28 added new battery powered board and changed lots of other stuff
2014-03-03 ignore eagle files for libraries
2014-03-03 added stm uc board
2014-03-03 small fixes to stm uc board
2014-03-03 changed battery sensing line on battery board to fit stm uc board
2014-03-03 added fabrication board
2014-03-04 version with more space to border and smaller diameter of debug connectors
2014-03-04 made drills of debug connectors smaller
2014-03-06 corrected the attributes
2014-03-06 chagned attribute
2014-03-14 added starting point for sw development and included my fancy but badly named framework
2014-03-14 minor cleanup
2014-03-14 fixed that
2014-03-14 adjusted flash script for homa use
2014-03-14 adjusted gitignore for our purposes
2014-03-14 corrected flashGDB script
2014-03-14 added documentations of processor
2014-03-14 added ggpio test
2014-03-20 moved lutzens framework (lfw) to a subfolder
2014-03-20 added no framework (nfw) files for easy experimention with the chip
2014-03-20 added gitmodules
2014-03-21 moved eclipse project files as well
2014-03-21 changed makefile a bit
2014-03-22 added spi starting point
2014-03-24 spi finally outputting something... lutz you are right: libopencm3 is pretty shitty
2014-03-25 changed spi to sw SS
2014-03-26 added very simple nrf driver which should send out a packet. still untested. performance of spi transfer sucks but at least it is something to start working with.
2014-03-26 RF receiver working together with nordic FOB. upon receiving a packet the red led is toggled
2014-04-06 added rtc and pwr stuff
2014-04-15 added simple power calculator
2014-04-15 tiny changes to power calculator
2014-04-24 added initial files for eeprom emulation, adc and temperature sensing. these are still not functional
2014-04-24 changed principle of operation of the battery powered nodes in the power calc
2014-04-25 added modified nordic fob source code (reduced payload from 4 to 2 bytes, switched to 250kbps)
2014-05-05 added ratios to power calculator
2014-05-06 added simple us sleep timer
2014-05-08 blubb
2014-05-21 Added a testing precompiler flag to overcome the need of commenting out the pull down and the standby mode for normal debugging
2014-06-20 fixed some timer stuff and added a test case in homa.c. still not functional
2014-06-20 added some adc stuff which was still uncommited on my machine. cant remember right now what I did back then...
2014-06-25 added initial version of the cr2032 powered board
2014-06-25 added some ignores to gitignore (map, elf, swp)
2014-06-27 adc is working now. time functionality as well (although currently it only does busy waiting)
2014-06-27 huge code cleanup. removed all warnings. created application source files for a simple temperature sensor, a (still nonfunctional) uart gateway and a wallsocket
2014-06-27 fixed bug in makefile. you can now choose the app to compile: make APP=TEMP
2014-06-28 changed the temperature node struct to a general node_status struct as all nodes can deliver this data. added a wakeup_count field which is incremented with each wakeup. added a non-volatile (at leas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
2014-06-28 moved some stuff to protocol.c. added advertise package which is sent from node to central with the 96bit unique id of the node. the central should then assign a 8bit node id to the advertiser
2014-06-28 made the nrf rx fifo checking code a bit more readable
2014-06-29 changed frequency to 2520MHz as this should be outside of the active WLAN frequencies
2014-07-08 added pullup/pulldown resistors to the rf pins ; connected PA0 (WKUP1) to external IO interface
2016-04-20 Added wiki contents to README
